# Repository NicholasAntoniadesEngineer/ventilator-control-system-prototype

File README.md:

# Ventilator Control System Prototypes (2021)

This repository contains three prototype implementations for ventilator control systems, each designed to test different approaches and hardware configurations. The project includes embedded C code for STM32 microcontrollers and a Python GUI application for real-time monitoring.

## Prototypes

### 1. Volume/Pressure Control Prototype
Located in `ventilator_volume_pressure/`, this implementation focuses on precise volume and pressure control using:
- Flow sensor (SFM3000) for volume measurement
- Honeywell pressure sensor for pressure monitoring
- Stepper motor control for volume delivery
- Real-time pressure and volume monitoring

### 2. Motor Control Prototype
Located in `ventilator_motor_control/`, this implementation emphasizes precise motor control for:
- Tidal volume delivery using stepper motors
- Position-based volume control
- TMCL motor driver integration
- State machine implementation for breathing cycles

### 3. CPAP Prototype
Located in `ventilator_cpap/`, this implementation provides:
- Continuous positive airway pressure control
- Dual valve control system
- Real-time pressure monitoring
- Simple pressure-based control loop

## Hardware Requirements

### Microcontroller
- STM32F4 series (NUCLEO-F439ZI recommended)

### Sensors
- SFM3000 flow sensor (I2C interface)
- Honeywell pressure sensor (I2C interface)
- Limit switches for motor positioning

### Actuators
- Stepper motor with driver (TMCL 1260 supported)
- Control valves (for CPAP prototype)
- GPIO-controlled indicators

### Communication
- USB-to-Serial adapter for GUI communication
- I2C bus for sensor communication
- Motor control interfaces (as needed)

## Software Requirements

### Development Environment
- STM32CubeIDE (or equivalent)
- Python 3.x for GUI application
- ARM GCC toolchain

### Python Dependencies
- numpy
- matplotlib
- tkinter
- pyserial

### STM32 Libraries
- STM32 HAL
- Custom BSP layer (provided)
- Sensor drivers (provided)

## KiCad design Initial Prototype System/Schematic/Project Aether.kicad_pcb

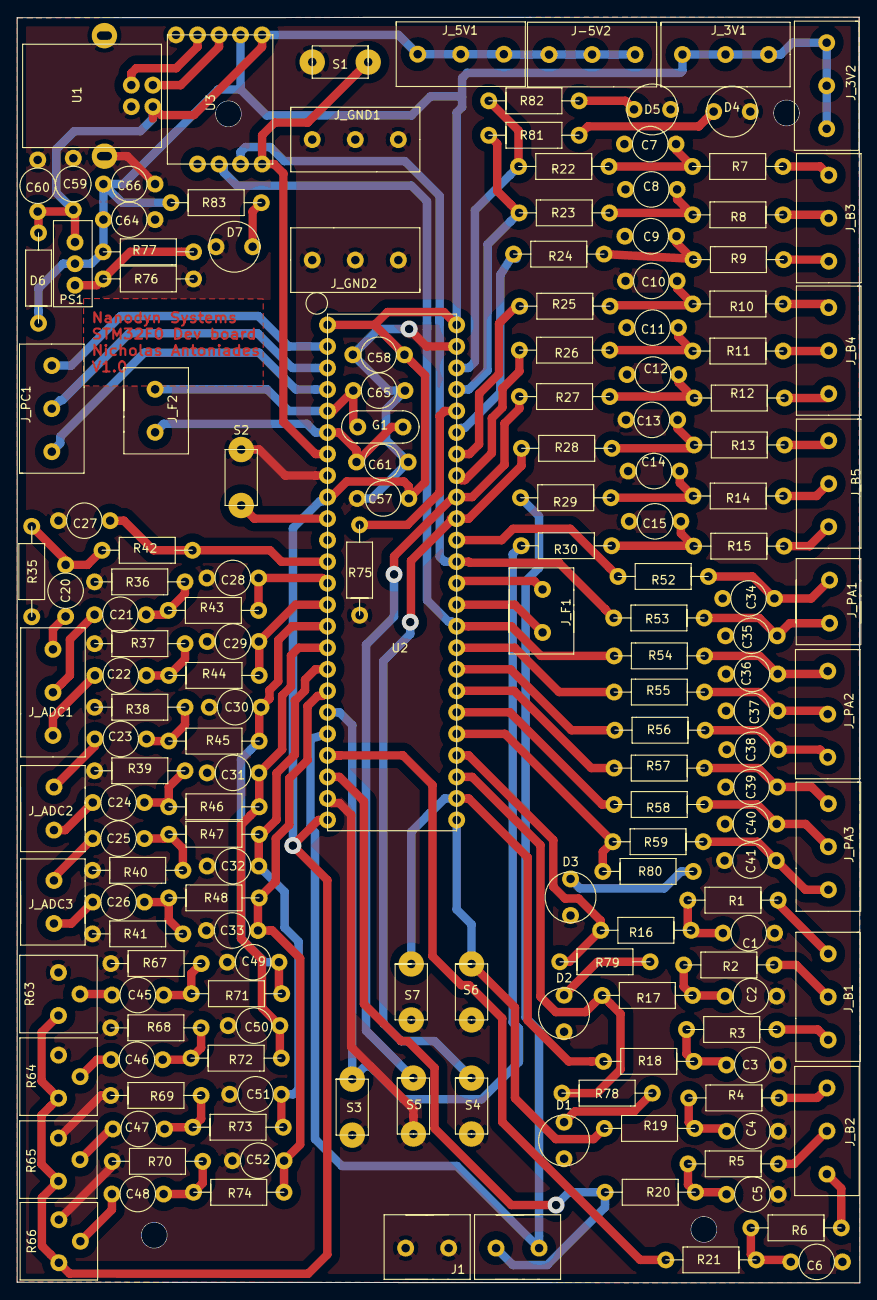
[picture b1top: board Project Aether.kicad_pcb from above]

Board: 2 copper layers, 99.4 x 149.4 mm, 166 parts (0 on the bottom side), 112 nets.

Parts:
C1, C2, C3, C4, C5, C6, C7, C8, C9, C10, C11, C12, C13, C14, C15, C20, C21, C22, C23, C24, C25, C26, C27, C28, C29, C30, C31, C32, C33, C34, C35, C36, C37, C38, C39, C40, C41, C45, C46, C47, C48, C49, C50, C51, C52, C59, C60, C61, C64, C65, C66: C
C57: 1u; C
C58: 100n; C
D1, D2, D3, D4, D5, D7: LED
D6: Diode
G1: Oscillator
J1: MotorHeader; MotorHeaders
J-5V2: 3-pinTerminal; 3-pin Terminal
J_3V1, J_3V2, J_5V1: 3-pinTerminal; 3-pin Terminal
J_ADC1: 3-pinTerminal; 3-pin Terminal
J_ADC2, J_ADC3: 2-pinTerminal; 2-pin Terminal
J_B1, J_B2, J_B3, J_B4, J_B5: 3-pinTerminal; 3-pin Terminal
J_F1, J_F2: 2-pinTerminal; 2-pin Terminal
J_GND1, J_GND2: 3-pinTerminal; 3-pin Terminal
J_PA1: 2-pinTerminal; 2-pin Terminal
J_PA2, J_PA3: 3-pinTerminal; 3-pin Terminal
J_PC1: 3-pinTerminal; 3-pin Terminal
PS1: LM317
R1, R2, R3, R4, R5, R6, R7, R8, R9, R10, R11, R12, R13, R14, R15, R16, R17, R18, R19, R20, R21, R22, R23, R24, R25, R26, R27, R28, R29, R30, R35, R36, R37, R38, R39, R40, R41, R42, R43, R44, R45, R46, R47, R48, R52, R53, R54, R55, R56, R57, R58, R59, R67, R68, R69, R70, R71, R72, R73, R74, R75, R76, R77, R83: R
R63, R64, R65, R66: Potentiometer; Potentiometers
R78, R79, R80, R81, R82: 100; R
S1, S2, S3, S4, S5, S6, S7: Button; Mini Button
U1: 61729-0010BLF
U2: STM32F051C6; STM32F51C6_Header
U3: STM32F1-debugger; STM32F1_Debugger

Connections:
+3V3: C57.1, C58.1, C64.1, C66.1, D6.1, J_3V1.1, J_3V1.2, J_3V1.3, J_3V2.1, J_3V2.2, J_3V2.3, PS1.2, R63.3, R64.3, R65.3, R66.3, R77.1, R83.1, U2.1, U2.9, U2.24, U2.48, U3.2
+5V: C59.1, C60.2, D6.2, J-5V2.1, J-5V2.2, J-5V2.3, J_5V1.1, J_5V1.2, J_5V1.3, PS1.3, U1.1, U3.1
/ADC2: C27.1, R42.2, U2.12
/ADC3: C28.1, R43.2, U2.13
/ADC4: C29.1, R44.2, U2.14
/ADC5: C30.1, C49.1, R45.2, R71.2, U2.15
/ADC6: C31.1, C50.1, R46.2, R72.2, U2.16
/ADC7: C32.1, C51.1, R47.2, R73.2, U2.17
/ADC8: C33.1, C52.1, R48.2, R74.2, U2.18
/Limit: R56.2, U2.32
/NRST: S1.2, U2.7, U3.9
/PA0: S2.2, U2.10
/PA8: R59.2, R80.1, U2.29
/PA12: R55.2, U2.33
/PA13: R54.2, U2.34, U3.7
/PA14: R53.2, U2.37, U3.8
/PA15: R52.2, U2.38
/PB1: R30.2, S3.2, U2.19
/PB2: J1.1, R29.2, U2.20
/PB3: R28.2, S4.2, U2.39
/PB4: R27.2, S5.2, U2.40
/PB5: R26.2, U2.41
/PB6: R25.2, U2.42
/PB7: R24.2, U2.43
/PB8: R23.2, R81.1, U2.45
/PB9: R22.2, R82.1, U2.46
/PB10: R21.2, U2.21
/PB11: J1.2, R20.2, U2.22
/PB12: R19.2, S6.2, U2.25
/PB13: R18.2, S7.2, U2.26
/PB14: R17.2, R78.1, U2.27
/PB15: R16.2, R79.1, U2.28
/PC13: J_PC1.3, U2.2
/PC14: J_PC1.2, U2.3
/PC15: J_PC1.1, U2.4
/PF0: C65.1, G1.2, J_F2.2, U2.5
/PF1: C61.1, G1.1, J_F2.1, U2.6
/PF6: J_F1.2, U2.35
/PF7: J_F1.1, U2.36
/UART_RX: R58.2, U2.30
/UART_TX: R57.2, U2.31
GNDREF: C1.2, C2.2, C3.2, C4.2, C5.2, C6.2, C7.2, C8.2, C9.2, C10.2, C11.2, C12.2, C13.2, C14.2, C15.2, C27.2, C28.2, C29.2, C30.2, C31.2, C32.2, C33.2, C34.2, C35.2, C36.2, C37.2, C38.2, C39.2, C40.2, C41.2, C49.2, C50.2, C51.2, C52.2, C57.2, C58.2, C59.2, C60.1, C61.2, C64.2, C65.2, C66.2, D1.2, D2.2, D3.2, D4.2, D5.2, D7.2, J1.3, J1.4, J_GND1.1, J_GND1.2, J_GND1.3, J_GND2.1, J_GND2.2, J_GND2.3, R35.1, R36.1, R37.1, R38.1, R39.1, R40.1, R41.1, R63.1, R64.1, R65.1, R66.1, R67.1, R68.1, R69.1, R70.1, R75.1, R76.2, S1.1, S2.1, S3.1, S4.1, S5.1, S6.1, S7.1, U1.4, U1.5, U1.6, U2.8, U2.23, U2.47, U3.5
unnamed: C1.1, R1.2, R16.1
unnamed: C2.1, R2.2, R17.1
unnamed: C3.1, R3.2, R18.1
unnamed: C4.1, R4.2, R19.1
unnamed: C5.1, R5.2, R20.1
unnamed: C6.1, R6.2, R21.1
unnamed: C7.1, R7.2, R22.1
unnamed: C8.1, R8.2, R23.1
unnamed: C9.1, R9.2, R24.1
unnamed: C10.1, R10.2, R25.1
unnamed: C11.1, R11.2, R26.1
unnamed: C12.1, R12.2, R27.1
unnamed: C13.1, R13.2, R28.1
unnamed: C14.1, R14.2, R29.1
unnamed: C15.1, R15.2, R30.1
unnamed: C20.1, J_ADC1.1
unnamed: C20.2, R35.2, R42.1
unnamed: C21.1, J_ADC1.2
unnamed: C21.2, R36.2, R43.1
unnamed: C22.1, J_ADC1.3
unnamed: C22.2, R37.2, R44.1
unnamed: C23.1, J_ADC2.1
unnamed: C23.2, R38.2, R45.1
unnamed: C24.1, J_ADC2.2
unnamed: C24.2, R39.2, R46.1
unnamed: C25.1, J_ADC3.1
unnamed: C25.2, R40.2, R47.1
unnamed: C26.1, J_ADC3.2
unnamed: C26.2, R41.2, R48.1
unnamed: C34.1, J_PA1.1, R52.1
unnamed: C35.1, J_PA1.2, R53.1
unnamed: C36.1, J_PA2.1, R54.1
unnamed: C37.1, J_PA2.2, R55.1
unnamed: C38.1, J_PA2.3, R56.1
unnamed: C39.1, J_PA3.1, R57.1
unnamed: C40.1, J_PA3.2, R58.1
unnamed: C41.1, J_PA3.3, R59.1
unnamed: C45.1, R63.2
unnamed: C45.2, R67.2, R71.1
unnamed: C46.1, R64.2
unnamed: C46.2, R68.2, R72.1
unnamed: C47.1, R65.2
unnamed: C47.2, R69.2, R73.1
unnamed: C48.1, R66.2
unnamed: C48.2, R70.2, R74.1
unnamed: D1.1, R78.2
unnamed: D2.1, R79.2
unnamed: D3.1, R80.2
unnamed: D4.1, R81.2
unnamed: D5.1, R82.2
unnamed: D7.1, R83.2
unnamed: J_B1.1, R1.1
unnamed: J_B1.2, R2.1
unnamed: J_B1.3, R3.1
unnamed: J_B2.1, R4.1
unnamed: J_B2.2, R5.1
unnamed: J_B2.3, R6.1
unnamed: J_B3.1, R7.1
unnamed: J_B3.2, R8.1
unnamed: J_B3.3, R9.1
unnamed: J_B4.1, R10.1
unnamed: J_B4.2, R11.1
unnamed: J_B4.3, R12.1
unnamed: J_B5.1, R13.1
unnamed: J_B5.2, R14.1
unnamed: J_B5.3, R15.1
unnamed: PS1.1, R76.1, R77.2
unnamed: R75.2, U2.44
unnamed: U1.2, U3.3
unnamed: U1.3, U3.4

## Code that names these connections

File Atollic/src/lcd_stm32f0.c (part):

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//* 1............VSS.......................GND                       *
//* 2............VDD.......................+5V                       *
//* 3............CONTRAST..................POT 2                     *
//* 4............RS  - Register Select.....PC14 (LCD_RS)             *
//* 5............RW  - Read/Write..........GND                       *
//* 6............E   - Enable..............PC15 (LCD_E)              *
//* 7............D0  - Data line 0.........GND                       *
//* 8............D1  - Data line 1.........GND                       *
//* 9............D2  - Data line 2.........GND                       *
//* 10...........D3  - Data line 3.........GND                       *
//* 11...........D4  - Data line 4.........PB8  (LCD_D4)             *
//* 12...........D5  - Data line 5.........PB9  (LCD_D5)             *
//* 13...........D6  - Data line 6.........PA12 (LCD_D6)             *
//* 14...........D7  - Data line 7.........PA15 (LCD_D7)             *
//* 15...........CATHLED...................NC                        *
//* 16...........ANODELED..................NC                        *
//********************************************************************
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{
    delay(20);                                  // Delay

    GPIOC->BSRR |= LCD_EN_SET;			      // pull E (PC15) HIGH

    delay(20);                                  // Delay

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
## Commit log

2021-04-28 Benchmark, Flushing the buffer for comms
2021-08-17 Rename Aether Light Display.py to Display.py
2021-08-17 Rename STM32f439ZIT6U Aether Light/.mxproject to STM32f439ZIT6U V/.mxproject
2021-08-17 Changes made
2024-10-19 Clean and organise code base
2024-10-19 Add README.md
2024-10-19 Rename file
2024-10-20 Cleaning up and reorganising code base
2024-10-20 Removing old files
2024-10-20 update libraries
2024-10-20 Organise additional files
2024-10-20 Reorganising files
2024-11-02 removing some old files
2024-11-02 add back files
2024-11-02 cleaning up
2024-11-02 cleaning repo
2024-11-09 Cleaning and updating
2024-11-09 Progress
2024-11-09 main.h fix
2024-11-09 Cleaning and organising
2024-11-09 moving files around
2024-11-09 tidy
2024-11-09 fix tab space
2024-11-09 update includes
2024-11-09 Refactor out motor control
2024-11-09 quick fix
2025-01-05 Add pdf of notes
2025-01-05 Cleaning up and updating code base
2025-01-06 Refactoring code
2025-01-06 refactoring codebase
2025-01-06 Rename folders
2025-01-06 refactoring comments
2025-01-06 renaming files appropriately
2025-01-06 updating bsp
2025-01-10 Adding some videos and photos
2025-01-15 update document pdf
2025-01-16 move file

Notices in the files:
Atollic/src/lcd_stm32f0.c:
WRITTEN BY: Copyright (C) Samuel Ginsberg 2004
